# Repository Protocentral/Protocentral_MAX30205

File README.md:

# Protocentral MAX30205 Body Temperature Sensor Library

Arduino library for the Protocentral MAX30205 human body temperature sensor breakout board.

## Don't have one? [Buy it here](https://protocentral.com/product/protocentral-max30205-body-temperature-sensor-breakout-board/)

You can buy the Qwiic-compatible MAX30205 [here](https://protocentral.com/product/protocentral-max30205-wearable-body-thermometer-breakout-board-qwiic-compatible/).

The QWIIC-compatible ProtoCentral MAX30205 breakout board is a wearable human body temperature sensor that reads with an accuracy of +/-0.1 °C. This is a digital I2C-based sensor, so no external ADC is required.

This version of the board is round and designed to be directly wearable by exposing an aluminium surface. The aluminium-base PCB helps in easy thermal conduction so that most of the heat gets transferred to the sensor, resulting in more accurate readings. The top side of the PCB is encapsulated in clear epoxy resin to make it waterproof, and it uses a medical-grade, biocompatible, flexible cable that does not irritate the skin.

## Features

- Digital I2C body temperature sensor — no external ADC needed
- High accuracy of +/-0.1 °C over the 37 °C to 39 °C range
- 16-bit resolution (1 LSB = 0.00390625 °C)
- Reads temperature in Celsius or Fahrenheit
- Automatic address scanning (0x48 / 0x49)
- Low-power shutdown mode (<3.5 µA)
- Works on any board with `Wire` (AVR, SAMD, ESP32, ESP8266, RP2040, STM32, and more)

## Installation

### Arduino Library Manager (Recommended)
1. Open the Arduino IDE
2. Go to **Sketch → Include Library → Manage Libraries**
3. Search for "Protocentral MAX30205"
4. Click **Install**

### Manual Installation
1. Download or clone this repository
2. Copy it into your Arduino libraries folder (`~/Documents/Arduino/libraries/`)

## Hardware Setup

Connect the breakout board to the Arduino as follows:

| MAX30205 pin | Arduino connection | Pin function |
|--------------|--------------------|--------------|
| Vin / 5V | Vin (3.3V also supported, change the solder jumper on the back; default is 5V) | Power supply |
| GND | GND | Ground |
| SDA | A4 (or the board's SDA pin) | Serial data |
| SCL | A5 (or the board's SCL pin) | Serial clock |

## Quick Start

```cpp
#include <Wire.h>
#include "Protocentral_MAX30205.h"

MAX30205 tempSensor;

void setup() {
  Serial.begin(115200);
  Wire.begin();

  // Scan for the sensor at 0x48 / 0x49 until one is found
  while (!tempSensor.scanAvailableSensors()) {
    Serial.println("Couldn't find the temperature sensor, please connect the sensor.");
    delay(5000);
  }

  tempSensor.begin();   // Continuous conversion, active mode
}

void loop() {
  Serial.print(tempSensor.getTemperature(), 2);
  Serial.println(" C");
  delay(100);
}
```

### Using a custom I2C bus or address

The constructor accepts an explicit I2C address and `TwoWire` instance:

```cpp
MAX30205 tempSensor(MAX30205_ADDRESS2, Wire1);   // 0x48 on the Wire1 bus
```

## API Reference

### Constructor

```cpp
MAX30205(uint8_t sensorAddress = MAX30205_ADDRESS1, TwoWire &wirePort = Wire)
```

### Methods

| Method | Description |
|--------|-------------|
| `begin()` | Configure continuous conversion mode; returns `true` if the sensor responds |
| `scanAvailableSensors()` | Probe addresses 0x48 and 0x49, latch the one that responds; returns `true` if found |
| `getTemperature()` | Read the body temperature in degrees Celsius |
| `getTemperatureF()` | Read the body temperature in degrees Fahrenheit |
| `shutdown()` | Put the device into low-power shutdown mode |
| `printRegisters()` | Dump the register contents to `Serial` for debugging |

### Constants

| Constant | Value | Description |
|----------|-------|-------------|
| `MAX30205_ADDRESS1` | `0x49` | Default I2C address |
| `MAX30205_ADDRESS2` | `0x48` | Alternate I2C address |
| `MAX30205_RESOLUTION` | `0.00390625` | Degrees Celsius per LSB |

## Examples

| Example | Description |
|---------|-------------|
| `01-basic-temperature-reading` | Print temperature in Celsius and Fahrenheit to the Serial Monitor |
| `02-temperature-serial-plotter` | Stream temperature to the Arduino Serial Plotter |

## Visualizing Output

Open the Arduino Serial Monitor (or Serial Plotter) at 115200 baud to view the readings.

## Documentation

For further details, refer to [the documentation on the MAX30205 breakout board](https://docs.protocentral.com/getting-started-with-MAX30205/).

## License

This product is open source! Both our hardware and software are open source and licensed under the following licenses:

**Hardware:** [Creative Commons Share-alike 4.0 International](http://creativecommons.org/licenses/by-sa/4.0/) 

**Software:** [MIT License](http://opensource.org/licenses/MIT)

**Documentation:** [Creative Commons Share-alike 4.0 International](http://creativecommons.org/licenses/by-sa/4.0/)

See [LICENSE.md](LICENSE.md) for the full license text.

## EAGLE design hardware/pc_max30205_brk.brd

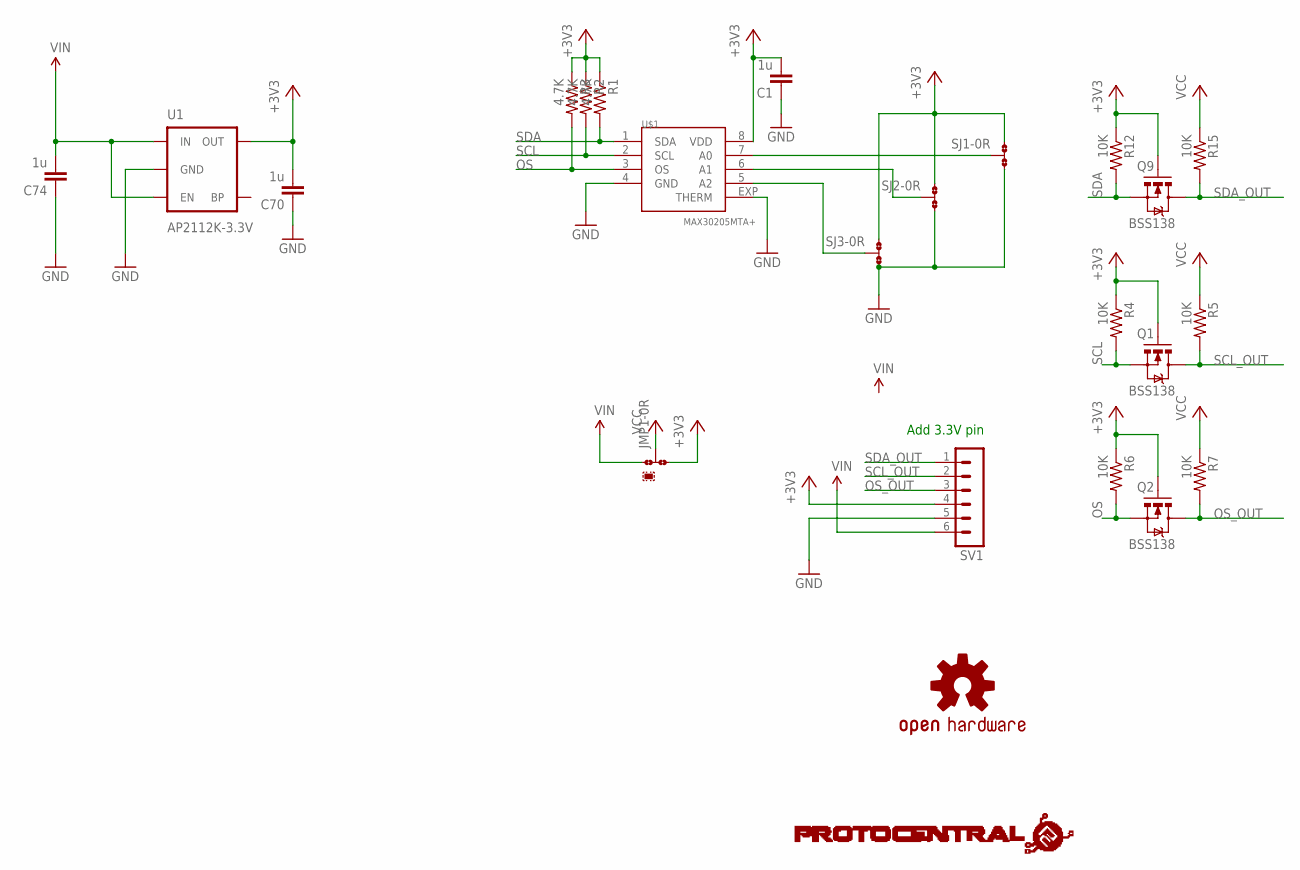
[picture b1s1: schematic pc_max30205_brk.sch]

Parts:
C1, C70, C74: 1u; C0805
JMP1: 0R-JUMPA; A0R-JMP-0402
Q1, Q2, Q9: BSS138; SOT23-3
R1, R2, R3: 4.7K; R0402
R4, R5, R6, R7, R12, R15: 10K; 0805
SJ1, SJ2, SJ3: 0R-JUMPA; A0R-JMP-0402
SV1: MA06-1
U1: AP2112K-3.3V; SOT23-5
U$1: MAX30205MTA+; TDFN-08
U$5: PROTY-LOGO; LOGO-PROTY
U$7: OSHW-LOGOS; OSHW-LOGO-S

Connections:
+3V3: C1.2, C70.2, JMP1.3, Q1.1 (G), Q2.1 (G), Q9.1 (G), R1.1, R2.1, R3.1, R4.1, R6.1, R12.1, SJ1.1, SJ2.1, SJ3.1, SV1.4, U1.5 (OUT), U$1.8 (VDD)
A0: SJ1.2, U$1.7 (A0)
A1: SJ2.2, U$1.6 (A1)
A2: SJ3.2, U$1.5 (A2)
GND: C1.1, C70.1, C74.1, SJ1.3, SJ2.3, SJ3.3, SV1.5, U1.2 (GND), U$1.4 (GND), U$1.EXP (THERM)
OS: Q2.2 (S), R3.2, R6.2, U$1.3 (OS)
OS_OUT: Q2.3 (D), R7.2, SV1.3
SCL: Q1.2 (S), R2.2, R4.2, U$1.2 (SCL)
SCL_OUT: Q1.3 (D), R5.2, SV1.2
SDA: Q9.2 (S), R1.2, R12.2, U$1.1 (SDA)
SDA_OUT: Q9.3 (D), R15.2, SV1.1
VCC: JMP1.2, R5.1, R7.1, R15.1
VIN: C74.2, JMP1.1, SV1.6, U1.1 (IN), U1.3 (EN)

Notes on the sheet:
Add 3.3V pin

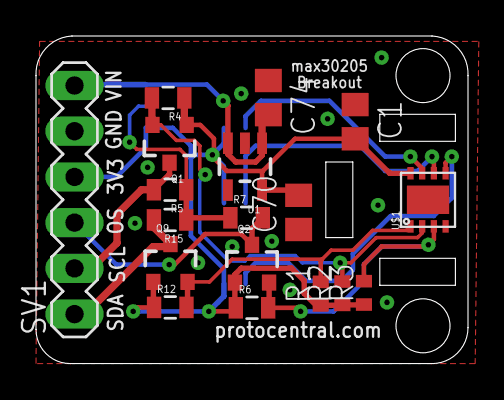
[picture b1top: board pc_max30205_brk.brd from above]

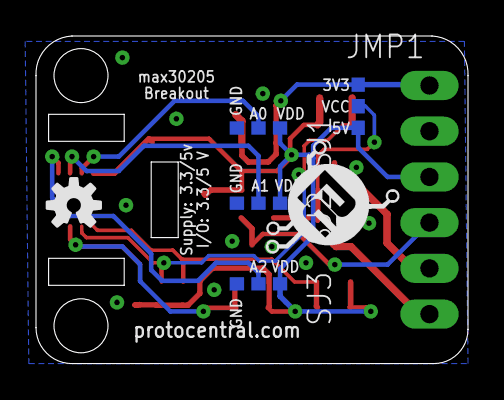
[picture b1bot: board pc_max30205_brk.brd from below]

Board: 4 copper layers, 24.0 x 18.2 mm, 24 parts (6 on the bottom side), 13 nets.

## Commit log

2016-12-29 upadated image
2016-12-29 Updated photo, links
2017-01-16 updated sketch
2018-04-19 Updated docs, images and Arduino library
2020-08-27 Fixed example sketch name issue
2023-03-25 Intermed commit
2023-03-25 Refactored two wire class
2023-03-25 Compiling. Untested
2023-03-25 Temp changes
2023-03-27 Working with hardcoded Wire1
2025-04-03 Workflow added, Readme updated, arduino library compatible with R4, version changed to 2.1.2
2025-04-30 documentation link updated
2026-06-01 Refactor library to Protocentral standard format and modern Arduino conventions
    - Add SPDX/MIT header blocks matching the Protocentral house style
    - Add include guard; remove invalid 'typedef unsigned char uint8_t'
    - Add constructor with configurable address and TwoWire bus; replace
    WIRE macro and rename I2C helpers to writeRegister/readRegister/readRegisters
    - begin() now returns bool; add getTemperatureF() and MAX30205_RESOLUTION
    - Add keywords.txt; update library.properties (email, includes, v3.0.0)

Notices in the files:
parts and their libraries:
SparkFun-PowerIC: Licensing: Creative Commons ShareAlike 4.0 International - https://creativecommons.org/licenses/by-sa/4.0
